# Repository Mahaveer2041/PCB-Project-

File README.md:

# PCB-Project-
Zine MCU/PCB Project 2023

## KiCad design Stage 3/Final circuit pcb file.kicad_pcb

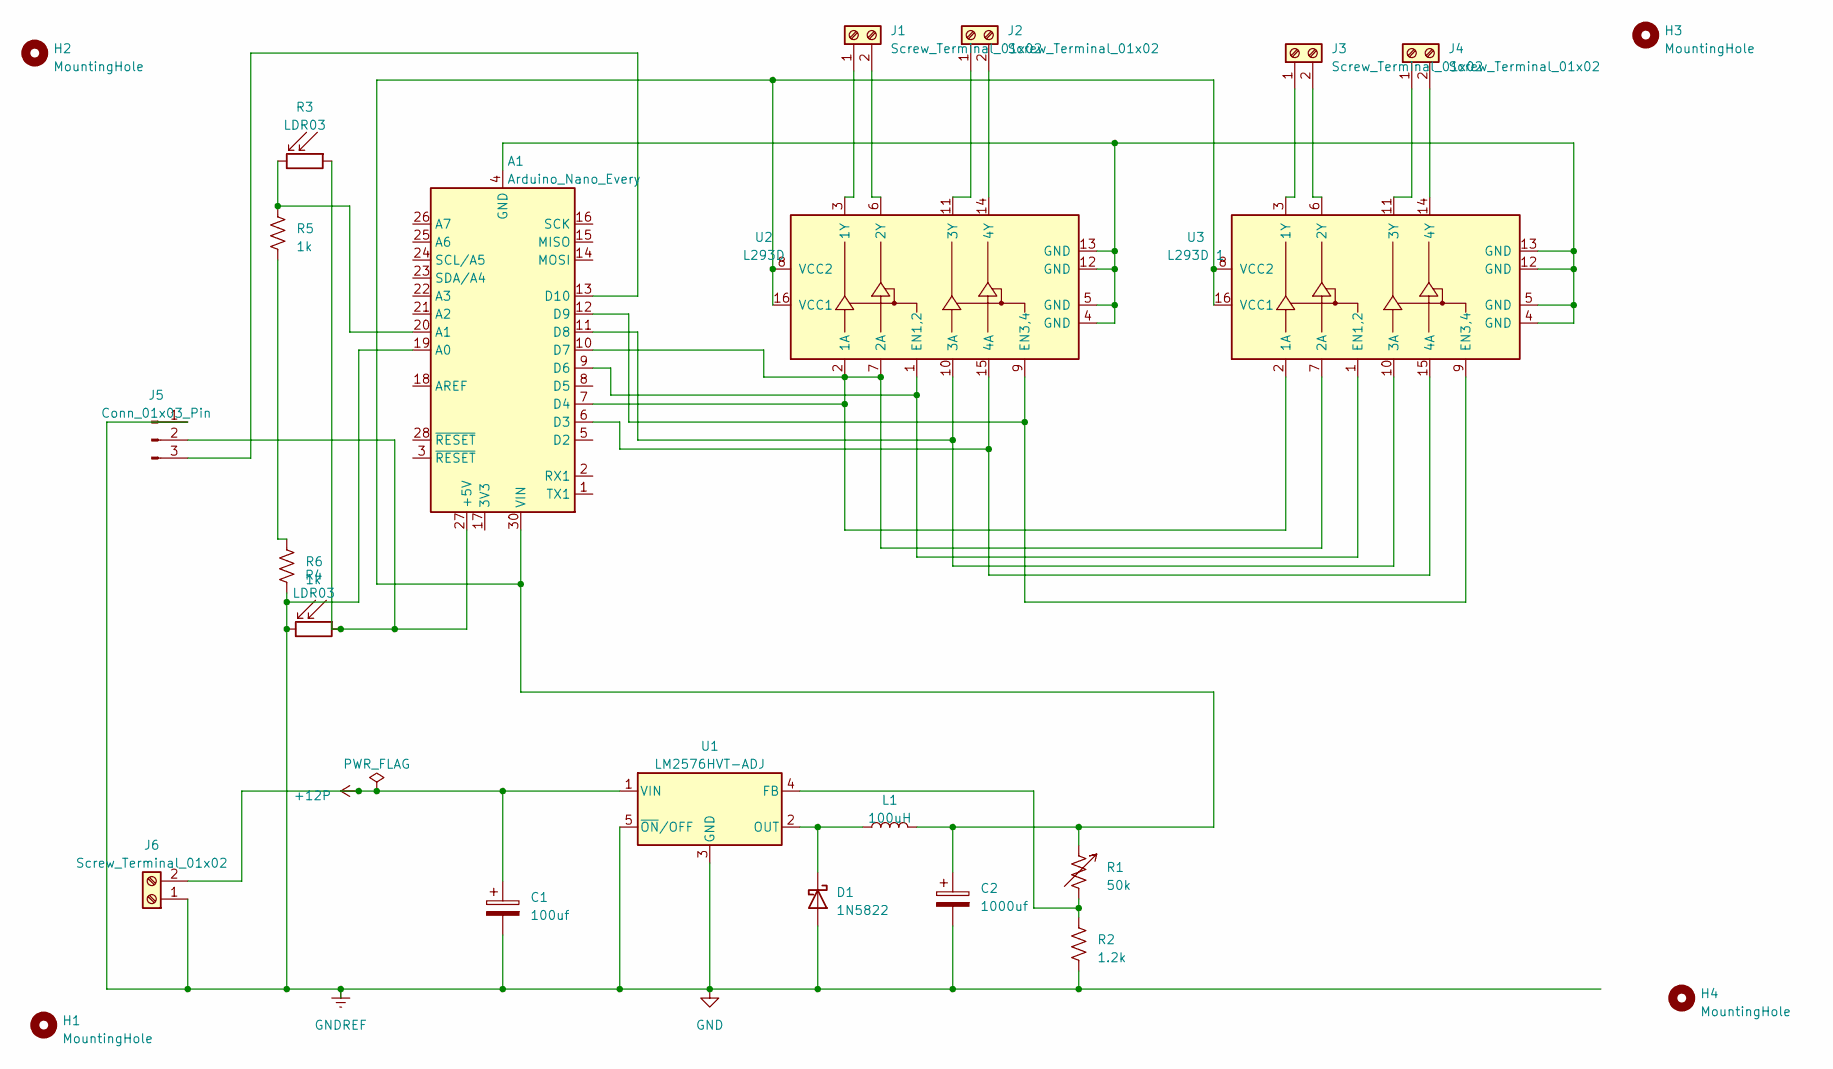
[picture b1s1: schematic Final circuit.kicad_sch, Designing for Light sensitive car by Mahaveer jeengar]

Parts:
A1: Arduino_Nano_Every; Arduino_Nano
C1: 100uf; CP_Axial_L10.0mm_D4.5mm_P15.00mm_Horizontal
C2: 1000uf; CP_Axial_L10.0mm_D4.5mm_P15.00mm_Horizontal
D1: 1N5822; D_DO-201AD_P15.24mm_Horizontal
H1, H2, H3, H4: MountingHole; MountingHole_2.1mm
J1, J2, J3, J4: Screw_Terminal_01x02; PinSocket_1x02_P2.54mm_Horizontal
J5: Conn_01x03_Pin; PinHeader_1x03_P1.00mm_Vertical
J6: Screw_Terminal_01x02; PhoenixContact_MCV_1,5_2-G-3.5_1x02_P3.50mm_Vertical
L1: 100uH; L_Axial_L6.6mm_D2.7mm_P10.16mm_Horizontal_Vishay_IM-2
R1: 50k; R_Axial_DIN0614_L14.3mm_D5.7mm_P15.24mm_Horizontal
R2: 1.2k; R_Axial_DIN0204_L3.6mm_D1.6mm_P1.90mm_Vertical
R3, R4: LDR03; R_LDR_10x8.5mm_P7.6mm_Vertical
R5, R6: 1k; R_Axial_DIN0204_L3.6mm_D1.6mm_P1.90mm_Vertical
U1: LM2576HVT-ADJ; TO-220-5_Vertical
U2: L293D; DIP-16_W7.62mm
U3: L293D 1; DIP-16_W7.62mm

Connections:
+12P: C1.1, J6.2, U1.1 (VIN)
GND: A1.19 (A0), C1.2, C2.2, D1.2 (A), J5.1, J6.1, R2.2, R4.2, R6.2, U1.3 (GND), U1.5 (~ON/OFF)
unnamed: A1.27 (+5V), J5.2, R3.1, R4.1
unnamed: A1.20 (A1), R3.2, R5.1
unnamed: A1.6 (D3), U2.15 (4A), U3.15 (4A)
unnamed: A1.7 (D4), A1.10 (D7), U2.2 (1A), U2.7 (2A), U3.2 (1A), U3.7 (2A)
unnamed: A1.9 (D6), U2.1 (EN1,2), U3.1 (EN1,2)
unnamed: A1.11 (D8), U2.10 (3A), U3.10 (3A)
unnamed: A1.12 (D9), U2.9 (EN3,4), U3.9 (EN3,4)
unnamed: A1.13 (D10), J5.3
unnamed: A1.4 (GND), A1.29 (GND), U2.4 (GND), U2.5 (GND), U2.12 (GND), U2.13 (GND), U3.4 (GND), U3.5 (GND), U3.12 (GND), U3.13 (GND)
unnamed: A1.30 (VIN), C2.1, L1.2, R1.1, U2.8 (VCC2), U2.16 (VCC1), U3.8 (VCC2), U3.16 (VCC1)
unnamed: D1.1 (K), L1.1, U1.2 (OUT)
unnamed: J1.1, U2.3 (1Y)
unnamed: J1.2, U2.6 (2Y)
unnamed: J2.1, U2.11 (3Y)
unnamed: J2.2, U2.14 (4Y)
unnamed: J3.1, U3.3 (1Y)
unnamed: J3.2, U3.6 (2Y)
unnamed: J4.1, U3.11 (3Y)
unnamed: J4.2, U3.14 (4Y)
unnamed: R5.2, R6.1
unnamed: R1.2, R2.1, U1.4 (FB)

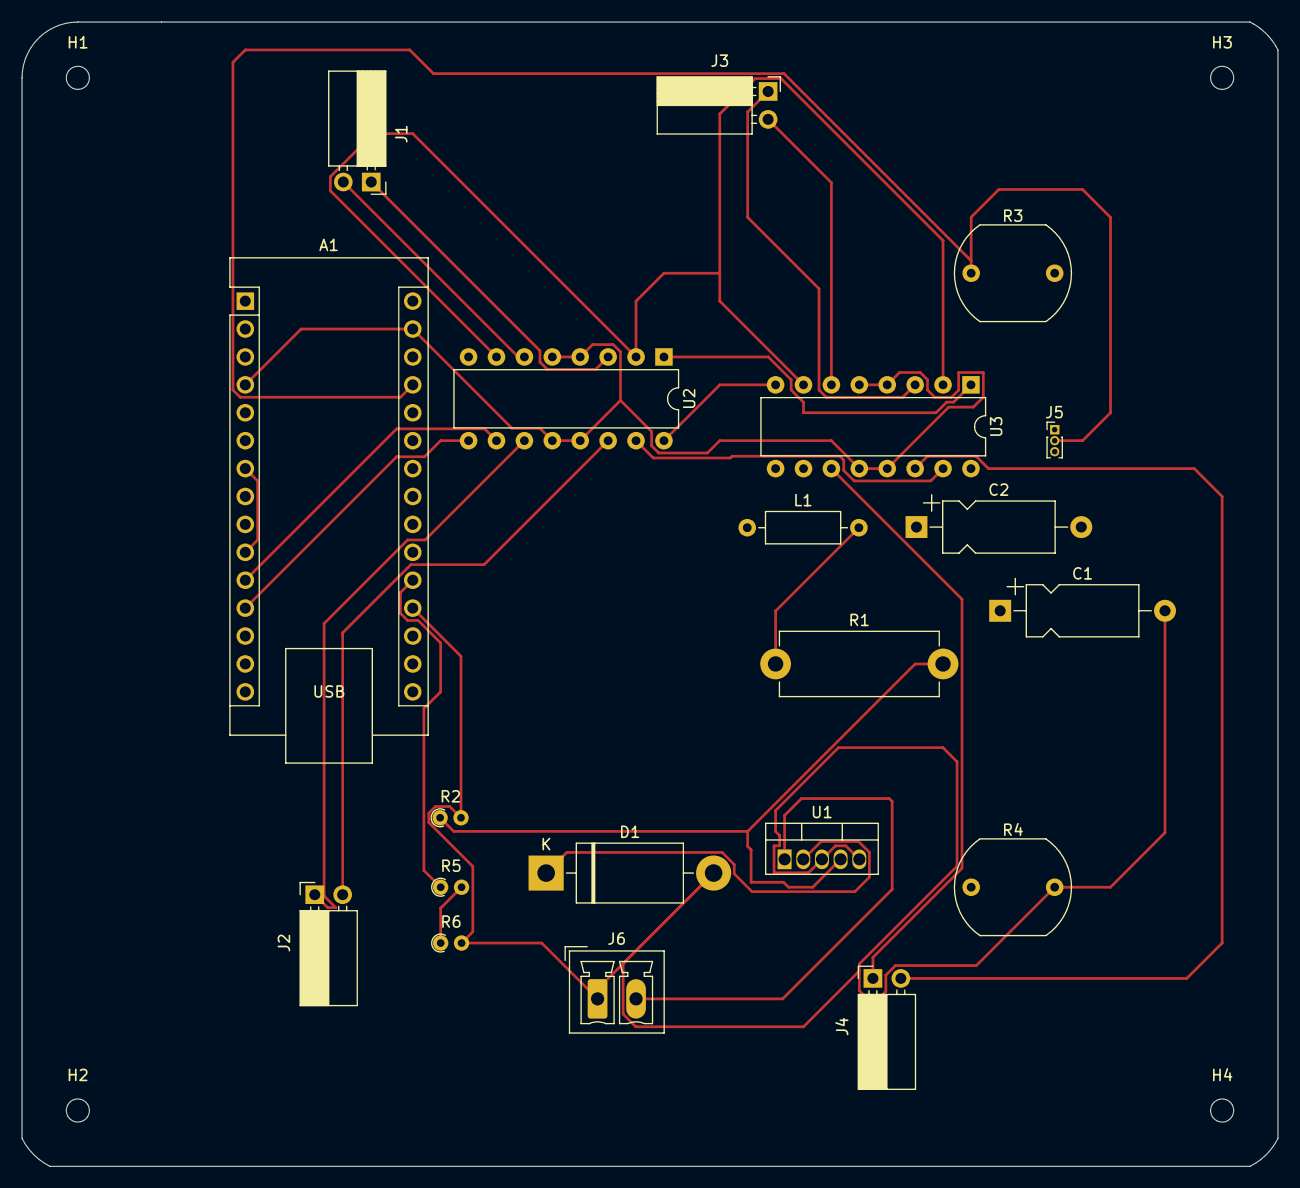
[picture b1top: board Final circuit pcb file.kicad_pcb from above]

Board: 2 copper layers, 114.3 x 104.1 mm, 24 parts (0 on the bottom side), 23 nets.
